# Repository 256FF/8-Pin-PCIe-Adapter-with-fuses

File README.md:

# 8-Pin-PCIe-Adapter-with-fuses
To avoid burning your PCB while testing a repaired GPU you can use this adapter

# License
Shield: [![CC BY-SA 4.0][cc-by-sa-shield]][cc-by-sa]

This work is licensed under a
[Creative Commons Attribution-ShareAlike 4.0 International License][cc-by-sa].

[![CC BY-SA 4.0][cc-by-sa-image]][cc-by-sa]

[cc-by-sa]: http://creativecommons.org/licenses/by-sa/4.0/
[cc-by-sa-image]: https://licensebuttons.net/l/by-sa/4.0/88x31.png
[cc-by-sa-shield]: https://img.shields.io/badge/License-CC%20BY--SA%204.0-lightgrey.svg

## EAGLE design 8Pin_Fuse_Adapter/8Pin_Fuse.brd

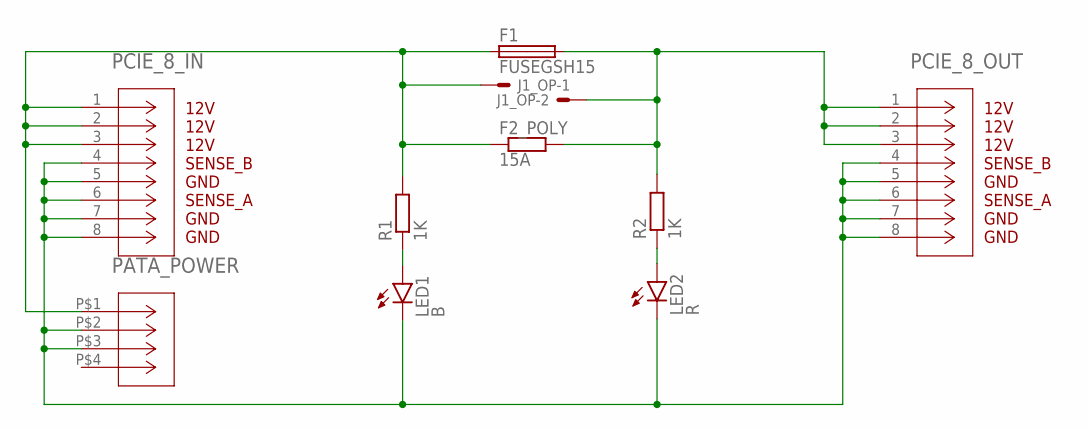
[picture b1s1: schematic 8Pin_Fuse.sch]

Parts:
F1: FUSEGSH15; SHK20Q
F2_POLY: 15A; M1206
J1_OP: 87758-0216
LED1: B; SML0805
LED2: R; SML0805
PATA_POWER: PATA_POWER
PCIE_8_IN, PCIE_8_OUT: 457180003A; CON_457180003_MOL
R1, R2: 1K; M0805

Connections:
12V: F1.1A, F2_POLY.1, J1_OP.1, PATA_POWER.P$1 (1), PCIE_8_IN.1, PCIE_8_IN.2, PCIE_8_IN.3, R1.2
12VO: F1.2A, F2_POLY.2, J1_OP.2, PCIE_8_OUT.1, PCIE_8_OUT.2, PCIE_8_OUT.3, R2.2
GND: LED1.C, LED2.C, PATA_POWER.P$2 (2), PATA_POWER.P$3 (3), PCIE_8_IN.4, PCIE_8_IN.5, PCIE_8_IN.6, PCIE_8_IN.7, PCIE_8_IN.8, PCIE_8_OUT.4, PCIE_8_OUT.5, PCIE_8_OUT.6, PCIE_8_OUT.7, PCIE_8_OUT.8
unnamed: LED2.A, R2.1
unnamed: LED1.A, R1.1

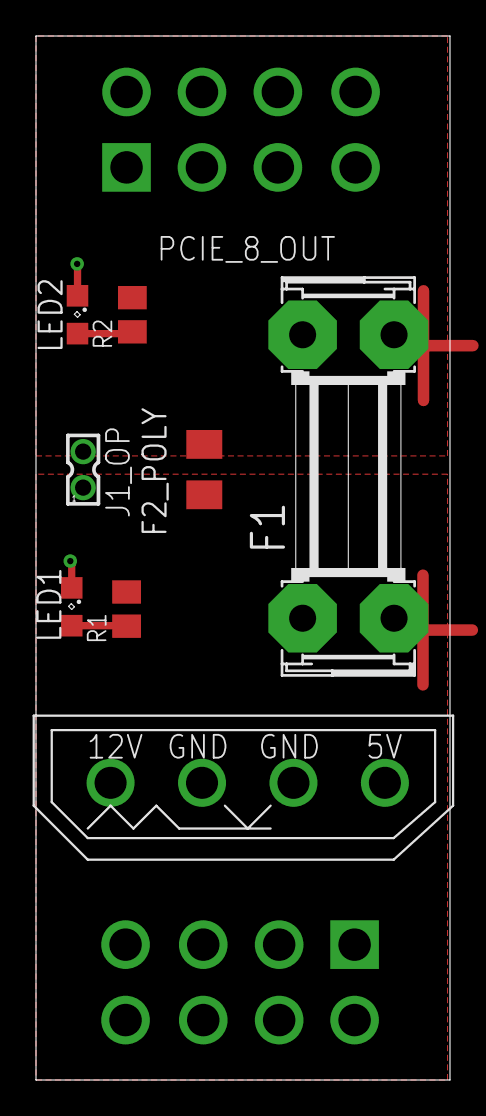
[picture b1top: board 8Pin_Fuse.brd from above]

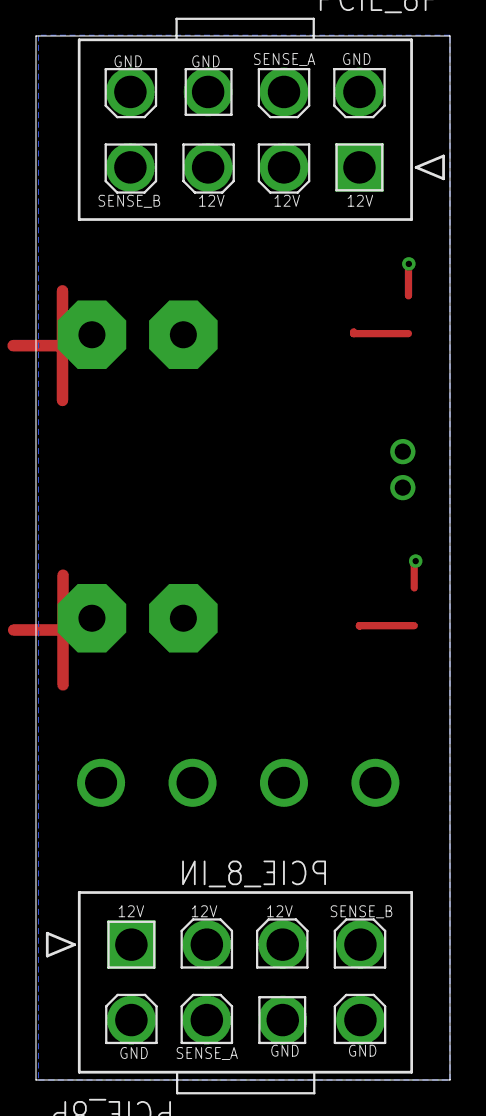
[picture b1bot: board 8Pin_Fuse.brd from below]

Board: 2 copper layers, 23.0 x 58.0 mm, 10 parts (2 on the bottom side), 5 nets.
